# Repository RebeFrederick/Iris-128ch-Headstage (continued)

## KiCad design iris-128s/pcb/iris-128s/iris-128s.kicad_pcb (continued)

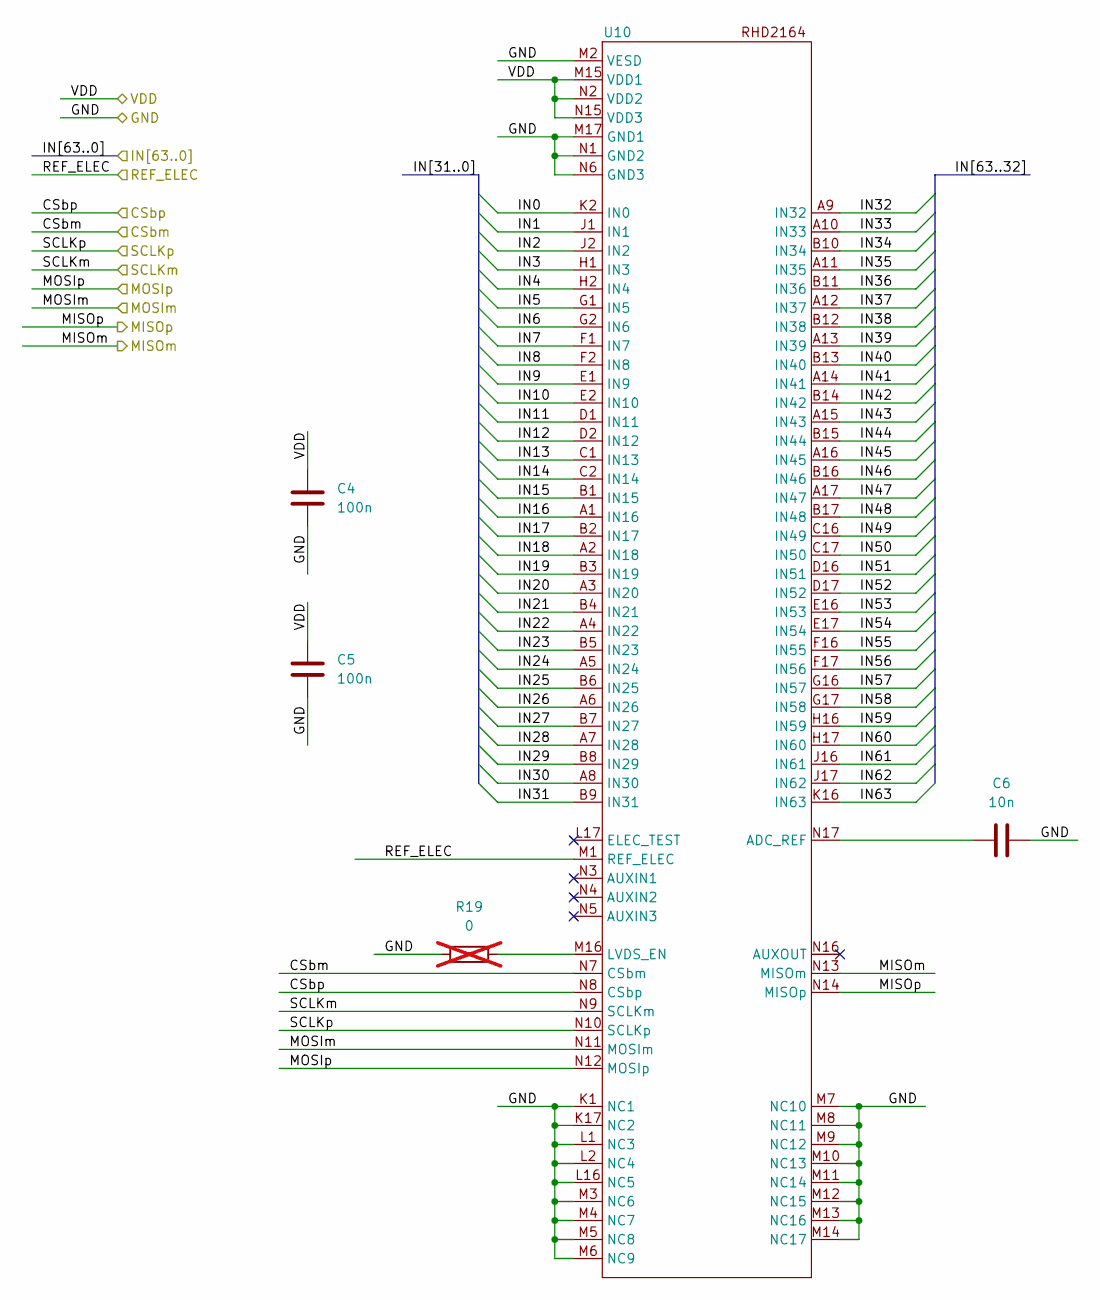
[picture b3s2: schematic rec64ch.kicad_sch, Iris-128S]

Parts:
C4, C5: 100n; C_0201_0603Metric; MPN C0603X5R1C104K030BC
C6: 10n; C_0201_0603Metric; MPN GRM033R61C103KA12D
R19: 0; R_0201_0603Metric; MPN RC0201FR-070RL; not fitted
U10: 104-Pin BGA - 9mmx7mm; MPN RHD2164

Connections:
/CSbm: U10.N7 (CSbm); also elsewhere on the board
/CSbp: U10.N8 (CSbp); also elsewhere on the board
/MISO2m: U10.N13 (MISOm); also elsewhere on the board
/MISO2p: U10.N14 (MISOp); also elsewhere on the board
/MOSIm: U10.N11 (MOSIm); also elsewhere on the board
/MOSIp: U10.N12 (MOSIp); also elsewhere on the board
/REC1IN0: U10.K2 (IN0); also elsewhere on the board
/REC1IN1: U10.J1 (IN1); also elsewhere on the board
/REC1IN2: U10.J2 (IN2); also elsewhere on the board
/REC1IN3: U10.H1 (IN3); also elsewhere on the board
/REC1IN4: U10.H2 (IN4); also elsewhere on the board
/REC1IN5: U10.G1 (IN5); also elsewhere on the board
/REC1IN6: U10.G2 (IN6); also elsewhere on the board
/REC1IN7: U10.F1 (IN7); also elsewhere on the board
/REC1IN8: U10.F2 (IN8); also elsewhere on the board
/REC1IN9: U10.E1 (IN9); also elsewhere on the board
/REC1IN10: U10.E2 (IN10); also elsewhere on the board
/REC1IN11: U10.D1 (IN11); also elsewhere on the board
/REC1IN12: U10.D2 (IN12); also elsewhere on the board
/REC1IN13: U10.C1 (IN13); also elsewhere on the board
/REC1IN14: U10.C2 (IN14); also elsewhere on the board
/REC1IN15: U10.B1 (IN15); also elsewhere on the board
/REC1IN16: U10.A1 (IN16); also elsewhere on the board
/REC1IN17: U10.B2 (IN17); also elsewhere on the board
/REC1IN18: U10.A2 (IN18); also elsewhere on the board
/REC1IN19: U10.B3 (IN19); also elsewhere on the board
/REC1IN20: U10.A3 (IN20); also elsewhere on the board
/REC1IN21: U10.B4 (IN21); also elsewhere on the board
/REC1IN22: U10.A4 (IN22); also elsewhere on the board
/REC1IN23: U10.B5 (IN23); also elsewhere on the board
/REC1IN24: U10.A5 (IN24); also elsewhere on the board
/REC1IN25: U10.B6 (IN25); also elsewhere on the board
/REC1IN26: U10.A6 (IN26); also elsewhere on the board
/REC1IN27: U10.B7 (IN27); also elsewhere on the board
/REC1IN28: U10.A7 (IN28); also elsewhere on the board
/REC1IN29: U10.B8 (IN29); also elsewhere on the board
/REC1IN30: U10.A8 (IN30); also elsewhere on the board
/REC1IN31: U10.B9 (IN31); also elsewhere on the board
/REC1IN32: U10.A9 (IN32); also elsewhere on the board
/REC1IN33: U10.A10 (IN33); also elsewhere on the board
/REC1IN34: U10.B10 (IN34); also elsewhere on the board
/REC1IN35: U10.A11 (IN35); also elsewhere on the board
/REC1IN36: U10.B11 (IN36); also elsewhere on the board
/REC1IN37: U10.A12 (IN37); also elsewhere on the board
/REC1IN38: U10.B12 (IN38); also elsewhere on the board
/REC1IN39: U10.A13 (IN39); also elsewhere on the board
/REC1IN40: U10.B13 (IN40); also elsewhere on the board
/REC1IN41: U10.A14 (IN41); also elsewhere on the board
/REC1IN42: U10.B14 (IN42); also elsewhere on the board
/REC1IN43: U10.A15 (IN43); also elsewhere on the board
/REC1IN44: U10.B15 (IN44); also elsewhere on the board
/REC1IN45: U10.A16 (IN45); also elsewhere on the board
/REC1IN46: U10.B16 (IN46); also elsewhere on the board
/REC1IN47: U10.A17 (IN47); also elsewhere on the board
/REC1IN48: U10.B17 (IN48); also elsewhere on the board
/REC1IN49: U10.C16 (IN49); also elsewhere on the board
/REC1IN50: U10.C17 (IN50); also elsewhere on the board
/REC1IN51: U10.D16 (IN51); also elsewhere on the board
/REC1IN52: U10.D17 (IN52); also elsewhere on the board
/REC1IN53: U10.E16 (IN53); also elsewhere on the board
/REC1IN54: U10.E17 (IN54); also elsewhere on the board
/REC1IN55: U10.F16 (IN55); also elsewhere on the board
/REC1IN56: U10.F17 (IN56); also elsewhere on the board
/REC1IN57: U10.G16 (IN57); also elsewhere on the board
/REC1IN58: U10.G17 (IN58); also elsewhere on the board
/REC1IN59: U10.H16 (IN59); also elsewhere on the board
/REC1IN60: U10.H17 (IN60); also elsewhere on the board
/REC1IN61: U10.J16 (IN61); also elsewhere on the board
/REC1IN62: U10.J17 (IN62); also elsewhere on the board
/REC1IN63: U10.K16 (IN63); also elsewhere on the board
/REF_ELEC: U10.M1 (REF_ELEC); also elsewhere on the board
/SCLKm: U10.N9 (SCLKm); also elsewhere on the board
/SCLKp: U10.N10 (SCLKp); also elsewhere on the board
GND1: C4.2, C5.2, C6.2, R19.1, U10.K1 (NC1), U10.K17 (NC2), U10.L1 (NC3), U10.L2 (NC4), U10.L16 (NC5), U10.M2 (VESD), U10.M3 (NC6), U10.M4 (NC7), U10.M5 (NC8), U10.M6 (NC9), U10.M7 (NC10), U10.M8 (NC11), U10.M9 (NC12), U10.M10 (NC13), U10.M11 (NC14), U10.M12 (NC15), U10.M13 (NC16), U10.M14 (NC17), U10.M17 (GND1), U10.N1 (GND2), U10.N6 (GND3); also elsewhere on the board
unnamed: C6.1, U10.N17 (ADC_REF)
unnamed: R19.2, U10.M16 (LVDS_EN)
VDD1: C4.1, C5.1, U10.M15 (VDD1), U10.N2 (VDD2), U10.N15 (VDD3); also elsewhere on the board

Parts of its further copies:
C1, C2: 100n; C_0201_0603Metric; MPN C0603X5R1C104K030BC
C3: 10n; C_0201_0603Metric; MPN GRM033R61C103KA12D
R10: 0; R_0201_0603Metric; MPN RC0201FR-070RL; not fitted
U9: 104-Pin BGA - 9mmx7mm; MPN RHD2164

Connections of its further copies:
/CSbm: U9.N7 (CSbm); also elsewhere on the board
/CSbp: U9.N8 (CSbp); also elsewhere on the board
/MISO1m: U9.N13 (MISOm); also elsewhere on the board
/MISO1p: U9.N14 (MISOp); also elsewhere on the board
/MOSIm: U9.N11 (MOSIm); also elsewhere on the board
/MOSIp: U9.N12 (MOSIp); also elsewhere on the board
/REC0IN0: U9.K2 (IN0); also elsewhere on the board
/REC0IN1: U9.J1 (IN1); also elsewhere on the board
/REC0IN2: U9.J2 (IN2); also elsewhere on the board
/REC0IN3: U9.H1 (IN3); also elsewhere on the board
/REC0IN4: U9.H2 (IN4); also elsewhere on the board
/REC0IN5: U9.G1 (IN5); also elsewhere on the board
/REC0IN6: U9.G2 (IN6); also elsewhere on the board
/REC0IN7: U9.F1 (IN7); also elsewhere on the board
/REC0IN8: U9.F2 (IN8); also elsewhere on the board
/REC0IN9: U9.E1 (IN9); also elsewhere on the board
/REC0IN10: U9.E2 (IN10); also elsewhere on the board
/REC0IN11: U9.D1 (IN11); also elsewhere on the board
/REC0IN12: U9.D2 (IN12); also elsewhere on the board
/REC0IN13: U9.C1 (IN13); also elsewhere on the board
/REC0IN14: U9.C2 (IN14); also elsewhere on the board
/REC0IN15: U9.B1 (IN15); also elsewhere on the board
/REC0IN16: U9.A1 (IN16); also elsewhere on the board
/REC0IN17: U9.B2 (IN17); also elsewhere on the board
/REC0IN18: U9.A2 (IN18); also elsewhere on the board
/REC0IN19: U9.B3 (IN19); also elsewhere on the board
/REC0IN20: U9.A3 (IN20); also elsewhere on the board
/REC0IN21: U9.B4 (IN21); also elsewhere on the board
/REC0IN22: U9.A4 (IN22); also elsewhere on the board
/REC0IN23: U9.B5 (IN23); also elsewhere on the board
/REC0IN24: U9.A5 (IN24); also elsewhere on the board
/REC0IN25: U9.B6 (IN25); also elsewhere on the board
/REC0IN26: U9.A6 (IN26); also elsewhere on the board
/REC0IN27: U9.B7 (IN27); also elsewhere on the board
/REC0IN28: U9.A7 (IN28); also elsewhere on the board
/REC0IN29: U9.B8 (IN29); also elsewhere on the board
/REC0IN30: U9.A8 (IN30); also elsewhere on the board
/REC0IN31: U9.B9 (IN31); also elsewhere on the board
/REC0IN32: U9.A9 (IN32); also elsewhere on the board
/REC0IN33: U9.A10 (IN33); also elsewhere on the board
/REC0IN34: U9.B10 (IN34); also elsewhere on the board
/REC0IN35: U9.A11 (IN35); also elsewhere on the board
/REC0IN36: U9.B11 (IN36); also elsewhere on the board
/REC0IN37: U9.A12 (IN37); also elsewhere on the board
/REC0IN38: U9.B12 (IN38); also elsewhere on the board
/REC0IN39: U9.A13 (IN39); also elsewhere on the board
/REC0IN40: U9.B13 (IN40); also elsewhere on the board
/REC0IN41: U9.A14 (IN41); also elsewhere on the board
/REC0IN42: U9.B14 (IN42); also elsewhere on the board
/REC0IN43: U9.A15 (IN43); also elsewhere on the board
/REC0IN44: U9.B15 (IN44); also elsewhere on the board
/REC0IN45: U9.A16 (IN45); also elsewhere on the board
/REC0IN46: U9.B16 (IN46); also elsewhere on the board
/REC0IN47: U9.A17 (IN47); also elsewhere on the board
/REC0IN48: U9.B17 (IN48); also elsewhere on the board
/REC0IN49: U9.C16 (IN49); also elsewhere on the board
/REC0IN50: U9.C17 (IN50); also elsewhere on the board
/REC0IN51: U9.D16 (IN51); also elsewhere on the board
/REC0IN52: U9.D17 (IN52); also elsewhere on the board
/REC0IN53: U9.E16 (IN53); also elsewhere on the board
/REC0IN54: U9.E17 (IN54); also elsewhere on the board
/REC0IN55: U9.F16 (IN55); also elsewhere on the board
/REC0IN56: U9.F17 (IN56); also elsewhere on the board
/REC0IN57: U9.G16 (IN57); also elsewhere on the board
/REC0IN58: U9.G17 (IN58); also elsewhere on the board
/REC0IN59: U9.H16 (IN59); also elsewhere on the board
/REC0IN60: U9.H17 (IN60); also elsewhere on the board
/REC0IN61: U9.J16 (IN61); also elsewhere on the board
/REC0IN62: U9.J17 (IN62); also elsewhere on the board
/REC0IN63: U9.K16 (IN63); also elsewhere on the board
/REF_ELEC: U9.M1 (REF_ELEC); also elsewhere on the board
/SCLKm: U9.N9 (SCLKm); also elsewhere on the board
/SCLKp: U9.N10 (SCLKp); also elsewhere on the board
GND1: C1.2, C2.2, C3.2, R10.1, U9.K1 (NC1), U9.K17 (NC2), U9.L1 (NC3), U9.L2 (NC4), U9.L16 (NC5), U9.M2 (VESD), U9.M3 (NC6), U9.M4 (NC7), U9.M5 (NC8), U9.M6 (NC9), U9.M7 (NC10), U9.M8 (NC11), U9.M9 (NC12), U9.M10 (NC13), U9.M11 (NC14), U9.M12 (NC15), U9.M13 (NC16), U9.M14 (NC17), U9.M17 (GND1), U9.N1 (GND2), U9.N6 (GND3); also elsewhere on the board
unnamed: C3.1, U9.N17 (ADC_REF)
unnamed: R10.2, U9.M16 (LVDS_EN)
VDD1: C1.1, C2.1, U9.M15 (VDD1), U9.N2 (VDD2), U9.N15 (VDD3); also elsewhere on the board

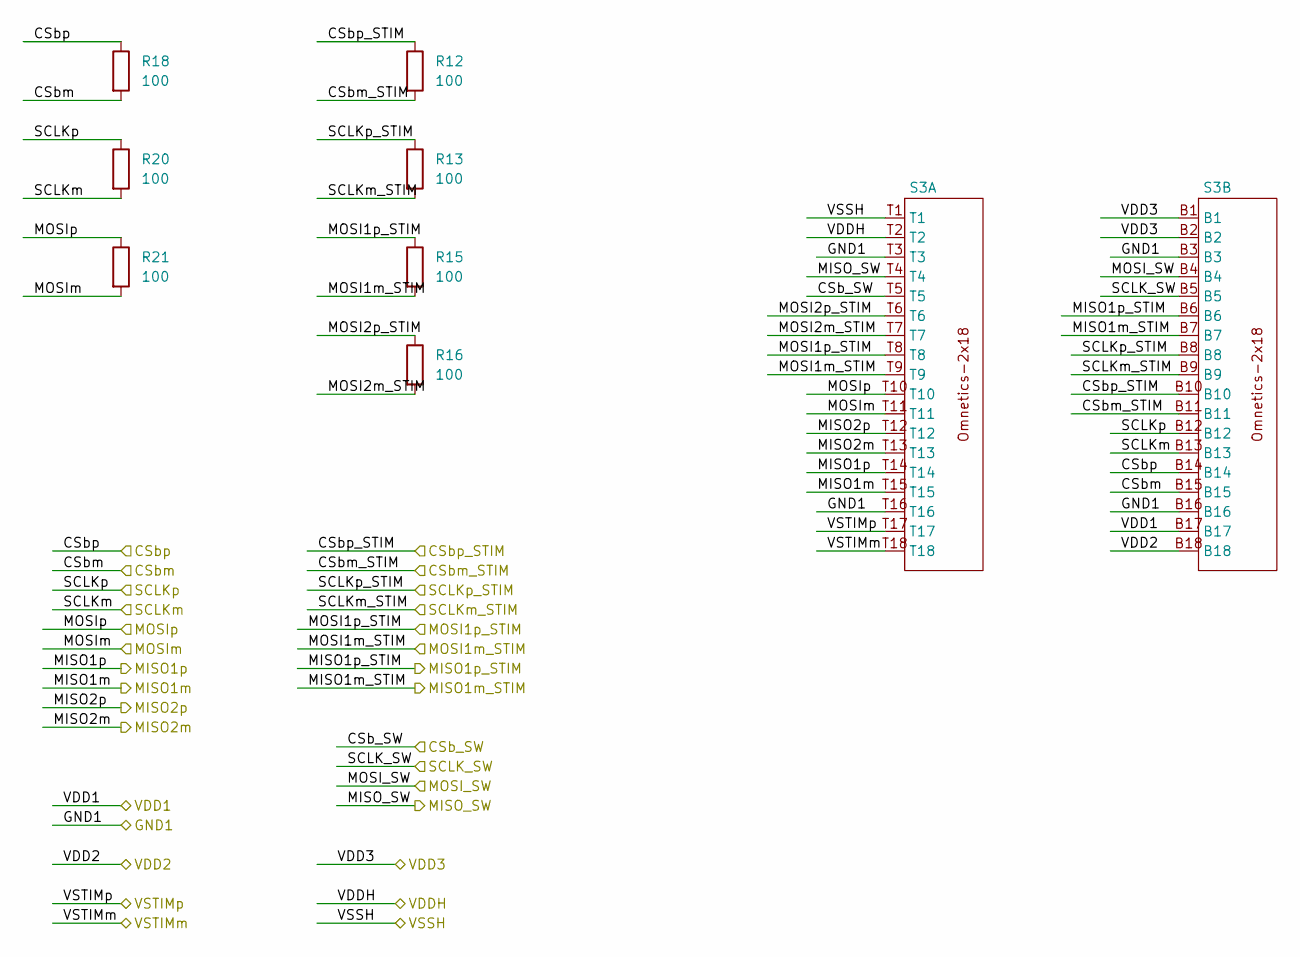
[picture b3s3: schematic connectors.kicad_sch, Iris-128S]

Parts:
R12, R13, R15, R16, R18, R20, R21: 100; R_0201_0603Metric; MPN RC0201FR-07100RL
S3: OMNETICS-A79024-001; MPN A79024-001

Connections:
/CSb_SW: S3.T5; also elsewhere on the board
/CSbm: R18.2, S3.B15; also elsewhere on the board
/CSbm_STIM: R12.2, S3.B11; also elsewhere on the board
/CSbp: R18.1, S3.B14; also elsewhere on the board
/CSbp_STIM: R12.1, S3.B10; also elsewhere on the board
/MISO1m: S3.T15; also elsewhere on the board
/MISO1p: S3.T14; also elsewhere on the board
/MISO2m: S3.T13; also elsewhere on the board
/MISO2p: S3.T12; also elsewhere on the board
/MISO_SW: S3.T4; also elsewhere on the board
/MISOm_STIM: S3.B7; also elsewhere on the board
/MISOp_STIM: S3.B6; also elsewhere on the board
/MOSI_SW: S3.B4; also elsewhere on the board
/MOSIm: R21.2, S3.T11; also elsewhere on the board
/MOSIm_STIM: R15.2, S3.T9; also elsewhere on the board
/MOSIp: R21.1, S3.T10; also elsewhere on the board
/MOSIp_STIM: R15.1, S3.T8; also elsewhere on the board
/SCLK_SW: S3.B5; also elsewhere on the board
/SCLKm: R20.2, S3.B13; also elsewhere on the board
/SCLKm_STIM: R13.2, S3.B9; also elsewhere on the board
/SCLKp: R20.1, S3.B12; also elsewhere on the board
/SCLKp_STIM: R13.1, S3.B8; also elsewhere on the board
/connectors/MOSI2m_STIM: R16.2, S3.T7
/connectors/MOSI2p_STIM: R16.1, S3.T6
GND1: S3.B3, S3.B16, S3.T3, S3.T16; also elsewhere on the board
VDD1: S3.B17; also elsewhere on the board
VDD2: S3.B18; also elsewhere on the board
VDD3: S3.B1, S3.B2; also elsewhere on the board
VDD_SW: S3.T2; also elsewhere on the board
VSS_SW: S3.T1; also elsewhere on the board
VSTIMm: S3.T18; also elsewhere on the board
VSTIMp: S3.T17; also elsewhere on the board

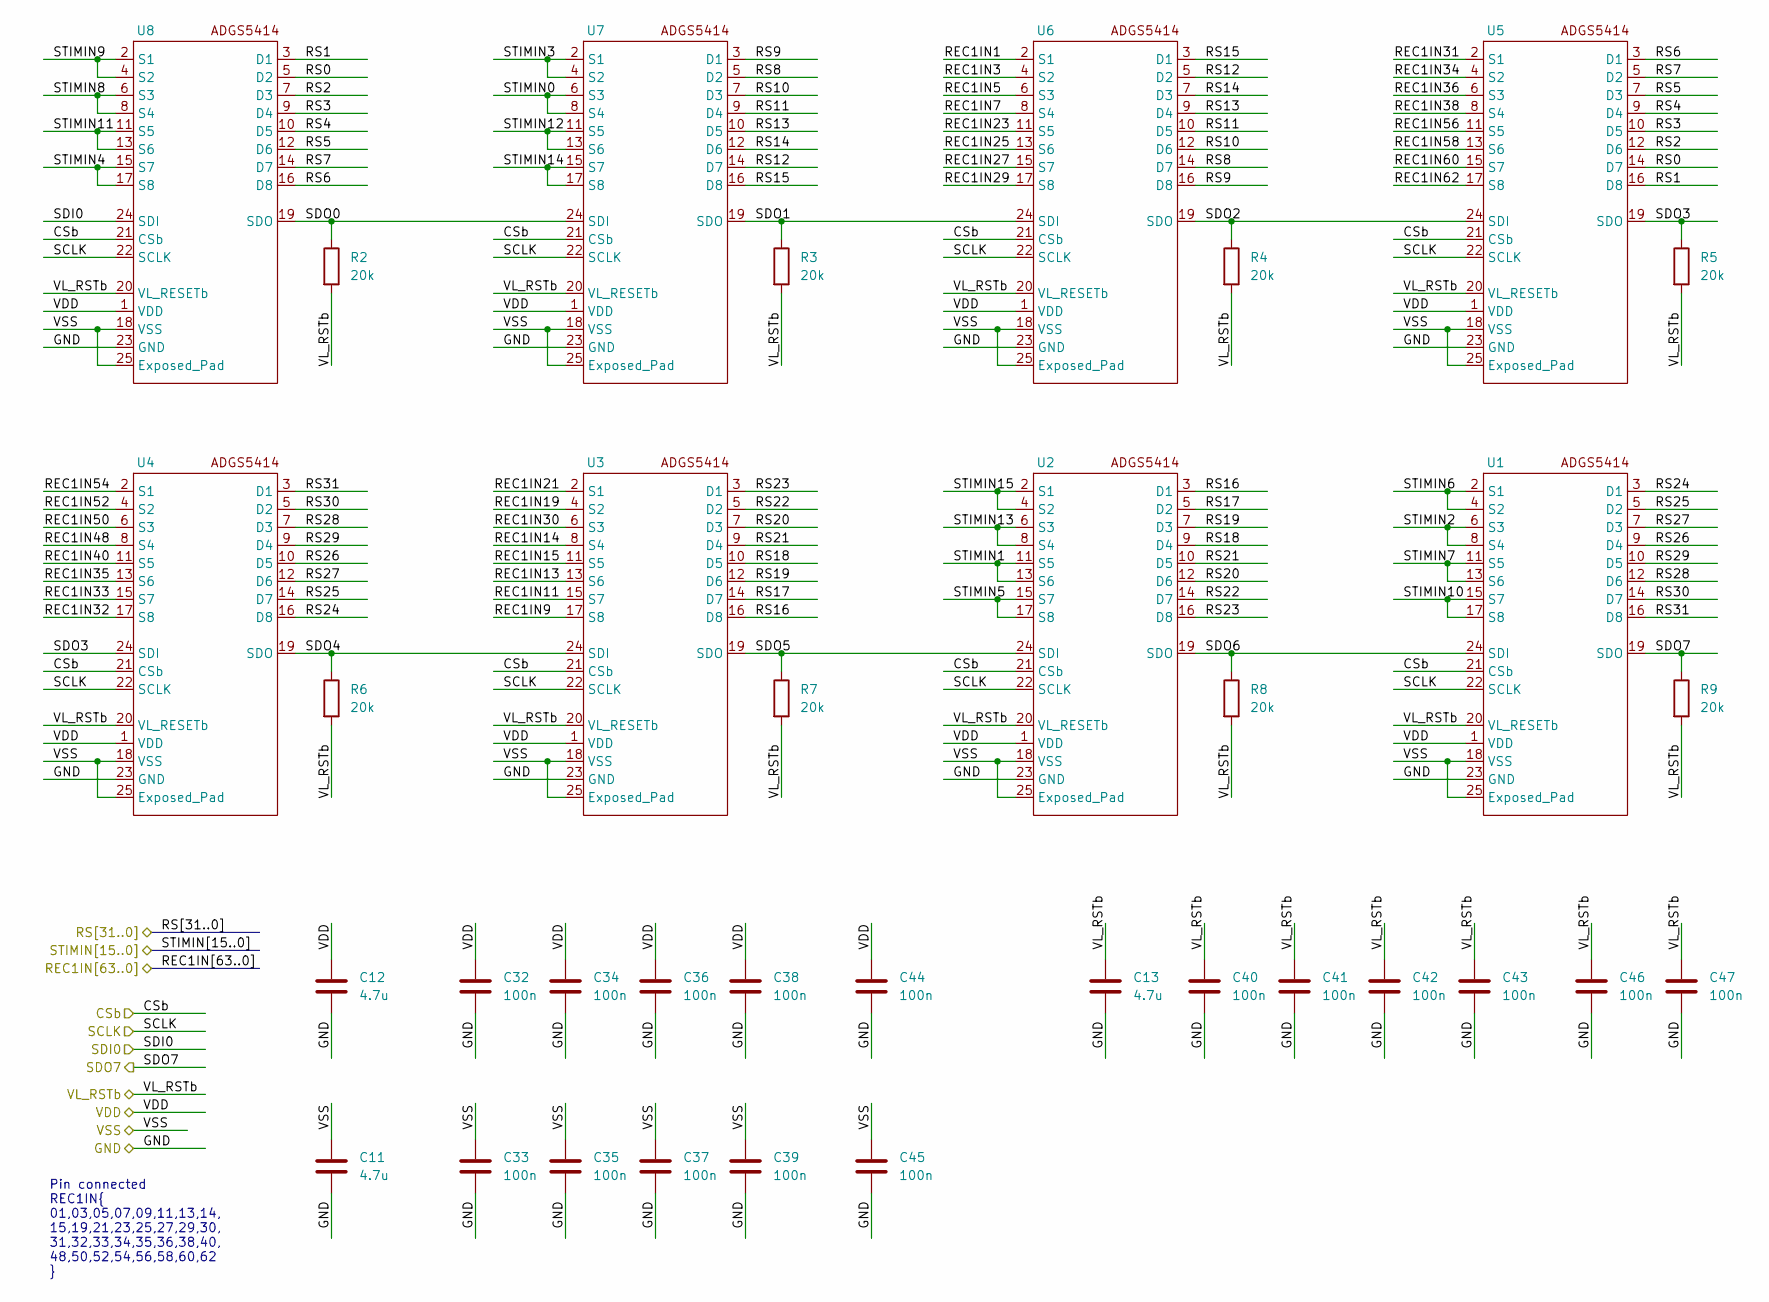
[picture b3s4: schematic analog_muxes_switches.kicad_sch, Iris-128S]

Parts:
C11, C12, C13: 4.7u; C_0402_1005Metric; MPN KGM05CR51C475MH
C32, C33, C34, C35, C36, C37, C38, C39, C40, C41, C42, C43, C44, C45, C46, C47: 100n; C_0201_0603Metric; MPN C0603X5R1C104K030BC
R2, R3, R4, R5, R6, R7, R8, R9: 20k; R_0201_0603Metric; MPN RC0201FR-0720KL
U1, U2, U3, U4, U5, U6, U7, U8: LFCSP-24-1EP_4mmx4mm_P0.5mm_EP2.6mm; MPN ADGS5414BCPZ

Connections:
/CSb_SW: U1.21 (CSb), U2.21 (CSb), U3.21 (CSb), U4.21 (CSb), U5.21 (CSb), U6.21 (CSb), U7.21 (CSb), U8.21 (CSb); also elsewhere on the board
/MISO_SW: R9.1, U1.19 (SDO); also elsewhere on the board
/MOSI_SW: U8.24 (SDI); also elsewhere on the board
/REC1IN1: U6.2 (S1); also elsewhere on the board
/REC1IN3: U6.4 (S2); also elsewhere on the board
/REC1IN5: U6.6 (S3); also elsewhere on the board
/REC1IN7: U6.8 (S4); also elsewhere on the board
/REC1IN9: U3.17 (S8); also elsewhere on the board
/REC1IN11: U3.15 (S7); also elsewhere on the board
/REC1IN13: U3.13 (S6); also elsewhere on the board
/REC1IN14: U3.8 (S4); also elsewhere on the board
/REC1IN15: U3.11 (S5); also elsewhere on the board
/REC1IN19: U3.4 (S2); also elsewhere on the board
/REC1IN21: U3.2 (S1); also elsewhere on the board
/REC1IN23: U6.11 (S5); also elsewhere on the board
/REC1IN25: U6.13 (S6); also elsewhere on the board
/REC1IN27: U6.15 (S7); also elsewhere on the board
/REC1IN29: U6.17 (S8); also elsewhere on the board
/REC1IN30: U3.6 (S3); also elsewhere on the board
/REC1IN31: U5.2 (S1); also elsewhere on the board
/REC1IN32: U4.17 (S8); also elsewhere on the board
/REC1IN33: U4.15 (S7); also elsewhere on the board
/REC1IN34: U5.4 (S2); also elsewhere on the board
/REC1IN35: U4.13 (S6); also elsewhere on the board
/REC1IN36: U5.6 (S3); also elsewhere on the board
/REC1IN38: U5.8 (S4); also elsewhere on the board
/REC1IN40: U4.11 (S5); also elsewhere on the board
/REC1IN48: U4.8 (S4); also elsewhere on the board
/REC1IN50: U4.6 (S3); also elsewhere on the board
/REC1IN52: U4.4 (S2); also elsewhere on the board
/REC1IN54: U4.2 (S1); also elsewhere on the board
/REC1IN56: U5.11 (S5); also elsewhere on the board
/REC1IN58: U5.13 (S6); also elsewhere on the board
/REC1IN60: U5.15 (S7); also elsewhere on the board
/REC1IN62: U5.17 (S8); also elsewhere on the board
/RS0: U5.14 (D7), U8.5 (D2); also elsewhere on the board
/RS1: U5.16 (D8), U8.3 (D1); also elsewhere on the board
/RS2: U5.12 (D6), U8.7 (D3); also elsewhere on the board
/RS3: U5.10 (D5), U8.9 (D4); also elsewhere on the board
/RS4: U5.9 (D4), U8.10 (D5); also elsewhere on the board
/RS5: U5.7 (D3), U8.12 (D6); also elsewhere on the board
/RS6: U5.3 (D1), U8.16 (D8); also elsewhere on the board
/RS7: U5.5 (D2), U8.14 (D7); also elsewhere on the board
/RS8: U6.14 (D7), U7.5 (D2); also elsewhere on the board
/RS9: U6.16 (D8), U7.3 (D1); also elsewhere on the board
/RS10: U6.12 (D6), U7.7 (D3); also elsewhere on the board
/RS11: U6.10 (D5), U7.9 (D4); also elsewhere on the board
/RS12: U6.5 (D2), U7.14 (D7); also elsewhere on the board
/RS13: U6.9 (D4), U7.10 (D5); also elsewhere on the board
/RS14: U6.7 (D3), U7.12 (D6); also elsewhere on the board
/RS15: U6.3 (D1), U7.16 (D8); also elsewhere on the board
/RS16: U2.3 (D1), U3.16 (D8); also elsewhere on the board
/RS17: U2.5 (D2), U3.14 (D7); also elsewhere on the board
/RS18: U2.9 (D4), U3.10 (D5); also elsewhere on the board
/RS19: U2.7 (D3), U3.12 (D6); also elsewhere on the board
/RS20: U2.12 (D6), U3.7 (D3); also elsewhere on the board
/RS21: U2.10 (D5), U3.9 (D4); also elsewhere on the board
/RS22: U2.14 (D7), U3.5 (D2); also elsewhere on the board
/RS23: U2.16 (D8), U3.3 (D1); also elsewhere on the board
/RS24: U1.3 (D1), U4.16 (D8); also elsewhere on the board
/RS25: U1.5 (D2), U4.14 (D7); also elsewhere on the board
/RS26: U1.9 (D4), U4.10 (D5); also elsewhere on the board
/RS27: U1.7 (D3), U4.12 (D6); also elsewhere on the board
/RS28: U1.12 (D6), U4.7 (D3); also elsewhere on the board
/RS29: U1.10 (D5), U4.9 (D4); also elsewhere on the board
/RS30: U1.14 (D7), U4.5 (D2); also elsewhere on the board
/RS31: U1.16 (D8), U4.3 (D1); also elsewhere on the board
/SCLK_SW: U1.22 (SCLK), U2.22 (SCLK), U3.22 (SCLK), U4.22 (SCLK), U5.22 (SCLK), U6.22 (SCLK), U7.22 (SCLK), U8.22 (SCLK); also elsewhere on the board
/STIMIN0: U7.6 (S3), U7.8 (S4); also elsewhere on the board
/STIMIN1: U2.11 (S5), U2.13 (S6); also elsewhere on the board
/STIMIN2: U1.6 (S3), U1.8 (S4); also elsewhere on the board
/STIMIN3: U7.2 (S1), U7.4 (S2); also elsewhere on the board
/STIMIN4: U8.15 (S7), U8.17 (S8); also elsewhere on the board
/STIMIN5: U2.15 (S7), U2.17 (S8); also elsewhere on the board
/STIMIN6: U1.2 (S1), U1.4 (S2); also elsewhere on the board
/STIMIN7: U1.11 (S5), U1.13 (S6); also elsewhere on the board
/STIMIN8: U8.6 (S3), U8.8 (S4); also elsewhere on the board
/STIMIN9: U8.2 (S1), U8.4 (S2); also elsewhere on the board
/STIMIN10: U1.15 (S7), U1.17 (S8); also elsewhere on the board
/STIMIN11: U8.11 (S5), U8.13 (S6); also elsewhere on the board
/STIMIN12: U7.11 (S5), U7.13 (S6); also elsewhere on the board
/STIMIN13: U2.6 (S3), U2.8 (S4); also elsewhere on the board
/STIMIN14: U7.15 (S7), U7.17 (S8); also elsewhere on the board
/STIMIN15: U2.2 (S1), U2.4 (S2); also elsewhere on the board
/analog_muxes_switches/SDO0: R2.1, U7.24 (SDI), U8.19 (SDO)
/analog_muxes_switches/SDO1: R3.1, U6.24 (SDI), U7.19 (SDO)
/analog_muxes_switches/SDO2: R4.1, U5.24 (SDI), U6.19 (SDO)
/analog_muxes_switches/SDO3: R5.1, U4.24 (SDI), U5.19 (SDO)
/analog_muxes_switches/SDO4: R6.1, U3.24 (SDI), U4.19 (SDO)
/analog_muxes_switches/SDO5: R7.1, U2.24 (SDI), U3.19 (SDO)
/analog_muxes_switches/SDO6: R8.1, U1.24 (SDI), U2.19 (SDO)
GND1: C11.2, C12.2, C13.2, C32.2, C33.2, C34.2, C35.2, C36.2, C37.2, C38.2, C39.2, C40.2, C41.2, C42.2, C43.2, C44.2, C45.2, C46.2, C47.2, U1.23 (GND), U2.23 (GND), U3.23 (GND), U4.23 (GND), U5.23 (GND), U6.23 (GND), U7.23 (GND), U8.23 (GND); also elsewhere on the board
VDD3: C13.1, C40.1, C41.1, C42.1, C43.1, C46.1, C47.1, R2.2, R3.2, R4.2, R5.2, R6.2, R7.2, R8.2, R9.2, U1.20 (VL_RESETb), U2.20 (VL_RESETb), U3.20 (VL_RESETb), U4.20 (VL_RESETb), U5.20 (VL_RESETb), U6.20 (VL_RESETb), U7.20 (VL_RESETb), U8.20 (VL_RESETb); also elsewhere on the board
VDD_SW: C12.1, C32.1, C34.1, C36.1, C38.1, C44.1, U1.1 (VDD), U2.1 (VDD), U3.1 (VDD), U4.1 (VDD), U5.1 (VDD), U6.1 (VDD), U7.1 (VDD), U8.1 (VDD); also elsewhere on the board
VSS_SW: C11.1, C33.1, C35.1, C37.1, C39.1, C45.1, U1.18 (VSS), U1.25 (Exposed_Pad), U2.18 (VSS), U2.25 (Exposed_Pad), U3.18 (VSS), U3.25 (Exposed_Pad), U4.18 (VSS), U4.25 (Exposed_Pad), U5.18 (VSS), U5.25 (Exposed_Pad), U6.18 (VSS), U6.25 (Exposed_Pad), U7.18 (VSS), U7.25 (Exposed_Pad), U8.18 (VSS), U8.25 (Exposed_Pad); also elsewhere on the board

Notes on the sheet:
Pin connected REC1IN{ 01,03,05,07,09,11,13,14, 15,19,21,23,25,27,29,30, 31,32,33,34,35,36,38,40, 48,50,52,54,56,58,60,62 }

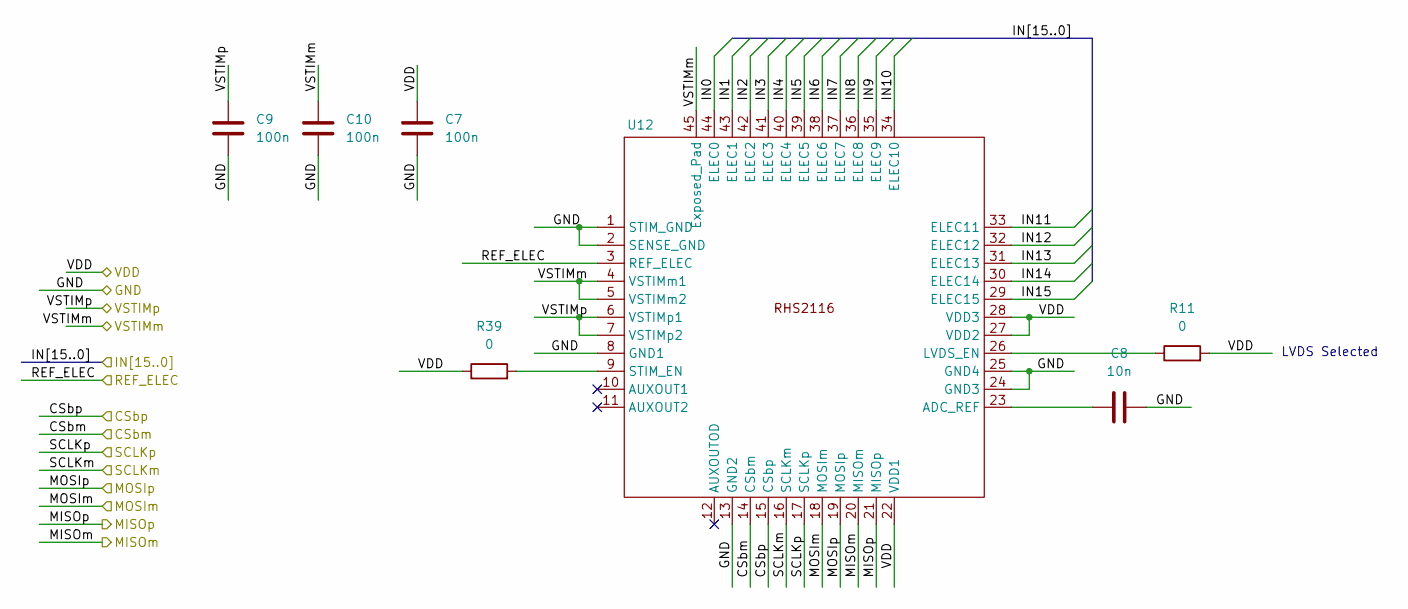
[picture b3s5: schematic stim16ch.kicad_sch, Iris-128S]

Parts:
C7, C9, C10: 100n; C_0201_0603Metric; MPN C0603X5R1C104K030BC
C8: 10n; C_0201_0603Metric; MPN GRM033R61C103KA12D
R11, R39: 0; R_0201_0603Metric; MPN RC0201FR-070RL
U12: QFN-44-1EP_7x7mm_P0.5mm_EP5.4x5.4mm; MPN RHS2116

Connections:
/CSbm_STIM: U12.14 (CSbm); also elsewhere on the board
/CSbp_STIM: U12.15 (CSbp); also elsewhere on the board
/MISOm_STIM: U12.20 (MISOm); also elsewhere on the board
/MISOp_STIM: U12.21 (MISOp); also elsewhere on the board
/MOSIm_STIM: U12.18 (MOSIm); also elsewhere on the board
/MOSIp_STIM: U12.19 (MOSIp); also elsewhere on the board
/REF_ELEC: U12.3 (REF_ELEC); also elsewhere on the board
/SCLKm_STIM: U12.16 (SCLKm); also elsewhere on the board
/SCLKp_STIM: U12.17 (SCLKp); also elsewhere on the board
/STIMIN0: U12.44 (ELEC0); also elsewhere on the board
/STIMIN1: U12.43 (ELEC1); also elsewhere on the board
/STIMIN2: U12.42 (ELEC2); also elsewhere on the board
/STIMIN3: U12.41 (ELEC3); also elsewhere on the board
/STIMIN4: U12.40 (ELEC4); also elsewhere on the board
/STIMIN5: U12.39 (ELEC5); also elsewhere on the board
/STIMIN6: U12.38 (ELEC6); also elsewhere on the board
/STIMIN7: U12.37 (ELEC7); also elsewhere on the board
/STIMIN8: U12.36 (ELEC8); also elsewhere on the board
/STIMIN9: U12.35 (ELEC9); also elsewhere on the board
/STIMIN10: U12.34 (ELEC10); also elsewhere on the board
/STIMIN11: U12.33 (ELEC11); also elsewhere on the board
/STIMIN12: U12.32 (ELEC12); also elsewhere on the board
/STIMIN13: U12.31 (ELEC13); also elsewhere on the board
/STIMIN14: U12.30 (ELEC14); also elsewhere on the board
/STIMIN15: U12.29 (ELEC15); also elsewhere on the board
GND1: C7.2, C8.2, C9.2, C10.2, U12.1 (STIM_GND), U12.2 (SENSE_GND), U12.8 (GND1), U12.13 (GND2), U12.24 (GND3), U12.25 (GND4); also elsewhere on the board
unnamed: C8.1, U12.23 (ADC_REF)
unnamed: R11.1, U12.26 (LVDS_EN)
unnamed: R39.2, U12.9 (STIM_EN)
VDD2: C7.1, R11.2, R39.1, U12.22 (VDD1), U12.27 (VDD2), U12.28 (VDD3); also elsewhere on the board
VSTIMm: C10.1, U12.4 (VSTIMm1), U12.5 (VSTIMm2), U12.45 (Exposed_Pad); also elsewhere on the board
VSTIMp: C9.1, U12.6 (VSTIMp1), U12.7 (VSTIMp2); also elsewhere on the board

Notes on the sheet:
LVDS Selected
